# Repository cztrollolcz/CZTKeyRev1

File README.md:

# CZTKeyRev1
 
Acrylic cutting: https://www.sculpteo.com/en/shop/cart/

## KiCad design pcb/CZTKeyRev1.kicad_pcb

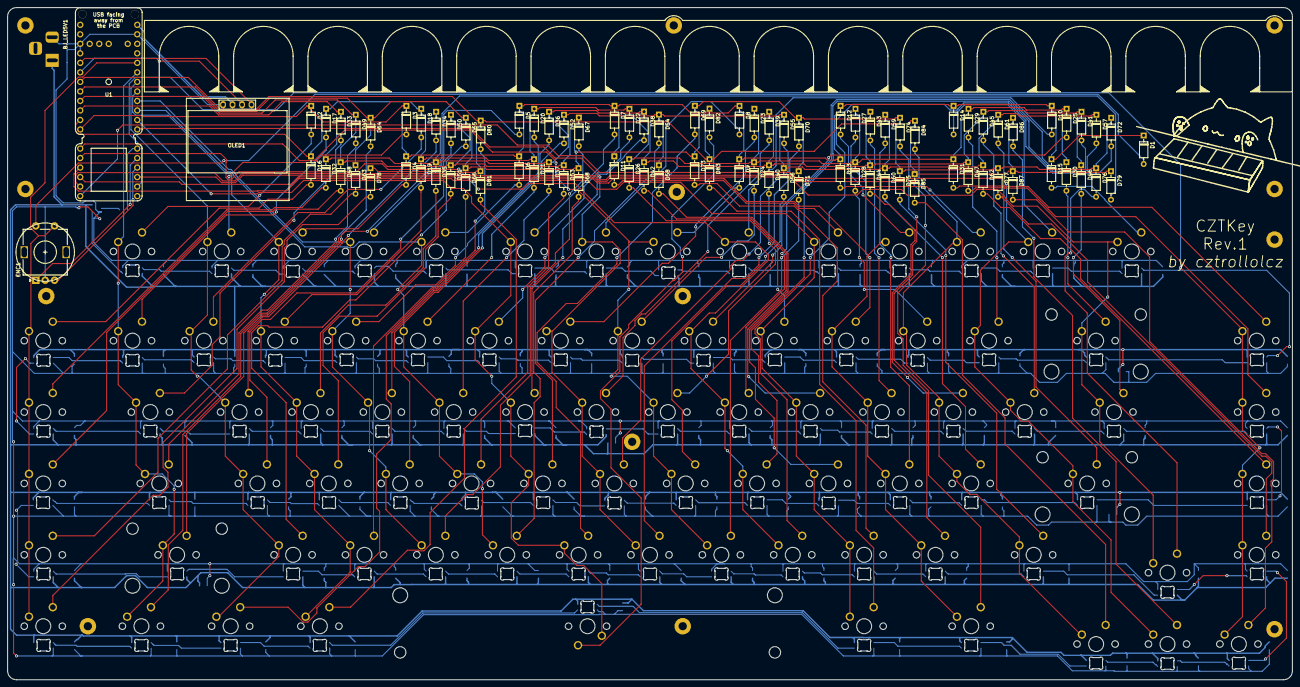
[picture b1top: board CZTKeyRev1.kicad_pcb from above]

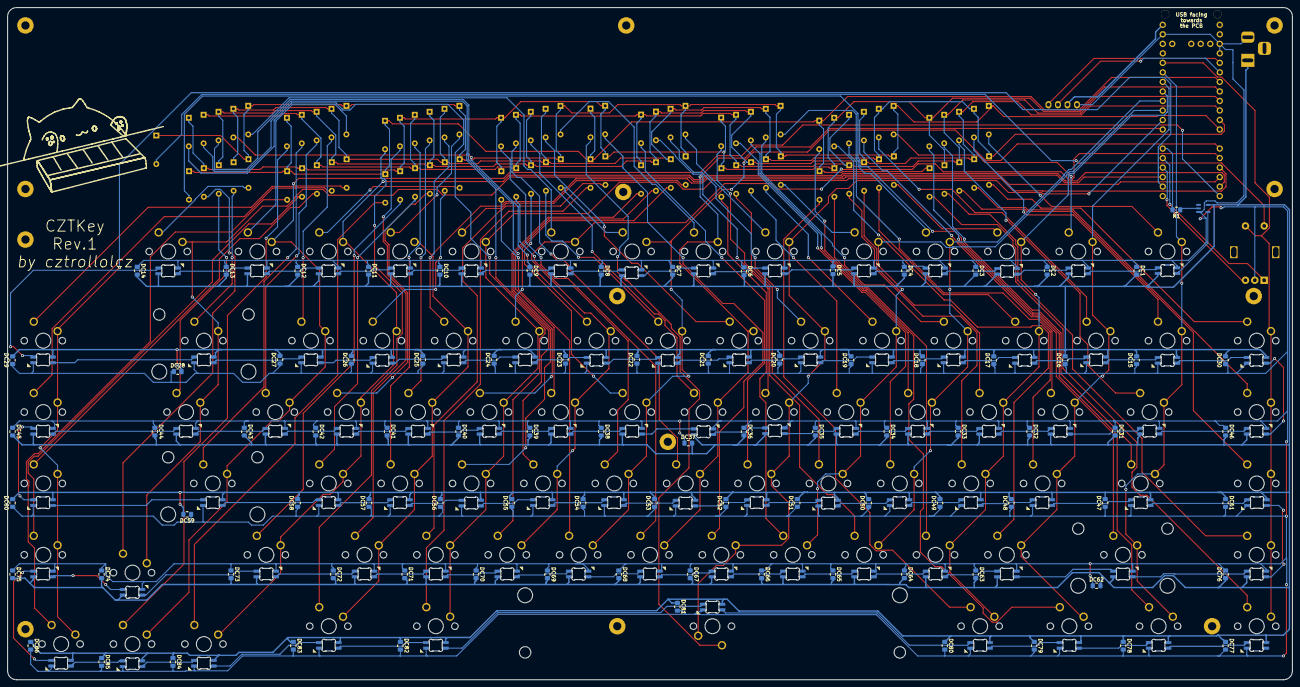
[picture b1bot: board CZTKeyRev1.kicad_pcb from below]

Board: 2 copper layers, 342.9 x 179.4 mm, 364 parts (88 on the bottom side), 204 nets.

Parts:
BJ_LED5V1: Barrel_Jack_Switch; BarrelJackP1
D1, D2, D3, D4, D5, D6, D7, D8, D9, D10, D11, D12, D13, D14, D15, D16, D17, D18, D19, D20, D21, D22, D23, D24, D25, D26, D27, D28, D29, D30, D31, D32, D33, D34, D35, D36, D37, D38, D39, D40, D41, D42, D43, D44, D45, D46, D47, D48, D49, D50, D51, D52, D53, D54, D55, D56, D57, D58, D59, D60, D61, D62, D63, D64, D65, D66, D67, D68, D69, D70, D71, D72, D73, D74, D75, D76, D77, D78, D79, D80, D81, D82, D83, D84, D85, D86, D87: D_Small; D_DO-35_SOD27_P7.62mm_Horizontal
DC1, DC2, DC3, DC4, DC5, DC6, DC7, DC8, DC9, DC10, DC11, DC12, DC13, DC14, DC15, DC16, DC17, DC18, DC19, DC20, DC21, DC22, DC23, DC24, DC25, DC26, DC27, DC28, DC29, DC30, DC31, DC32, DC33, DC34, DC35, DC36, DC37, DC38, DC39, DC40, DC41, DC42, DC43, DC44, DC45, DC46, DC47, DC48, DC49, DC50, DC51, DC52, DC53, DC54, DC55, DC56, DC57, DC58, DC59, DC60, DC61, DC62, DC63, DC64, DC65, DC66, DC67, DC68, DC69, DC70, DC71, DC72, DC73, DC74, DC75, DC76, DC77, DC78, DC79, DC80, DC81, DC82, DC83, DC84, DC85, DC86: 100n; C_0805_2012Metric_Pad1.15x1.40mm_HandSolder
ENC1: Rotary_Encoder_Switch; RotaryEncoder_Alps_EC11E-Switch_Vertical_H20mm
EXT_IC1: 74LVC1G17GV,125; SOT95P275X110-5N
LED1, LED2, LED3, LED4, LED5, LED6, LED7, LED8, LED9, LED10, LED11, LED12, LED13, LED14, LED15, LED16, LED17, LED18, LED19, LED20, LED21, LED22, LED23, LED24, LED25, LED26, LED27, LED28, LED29, LED30, LED31, LED32, LED33, LED34, LED35, LED36, LED37, LED38, LED39, LED40, LED41, LED42, LED43, LED44, LED45, LED46, LED47, LED48, LED49, LED50, LED51, LED52, LED53, LED54, LED55, LED56, LED57, LED58, LED59, LED60, LED61, LED62, LED63, LED64, LED65, LED66, LED67, LED68, LED69, LED70, LED71, LED72, LED73, LED74, LED75, LED76, LED77, LED78, LED79, LED80, LED81, LED82, LED83, LED84, LED85, LED86: YS-SK6812MINI-E; SK6812MINIE-simple
MX_1, MX_2, MX_3, MX_4, MX_5, MX_6, MX_7, MX_8, MX_9, MX_10: MX-NoLED; MXOnly-1U-NoLED
MX_A1: MX-NoLED; MXOnly-1U-NoLED
MX_ALT_L1: MX-NoLED; MXOnly-1.25U-NoLED
MX_ALT_R1: MX-NoLED; MXOnly-1.5U-NoLED
MX_B1: MX-NoLED; MXOnly-1U-NoLED
MX_BACKSPACE1: MX-NoLED; MXOnly-2U-NoLED
MX_BCKSLASH1: MX-NoLED; MXOnly-1.5U-NoLED
MX_BR_L1: MX-NoLED; MXOnly-1U-NoLED
MX_BR_R1: MX-NoLED; MXOnly-1U-NoLED
MX_C1: MX-NoLED; MXOnly-1U-NoLED
MX_CAPS1: MX-NoLED; MXOnly-1.75U-NoLED
MX_COMMA1: MX-NoLED; MXOnly-1U-NoLED
MX_CTRL_L1: MX-NoLED; MXOnly-1.25U-NoLED
MX_CTRL_R1: MX-NoLED; MXOnly-1.5U-NoLED
MX_D1: MX-NoLED; MXOnly-1U-NoLED
MX_DELETE1: MX-NoLED; MXOnly-1U-NoLED
MX_DOT1: MX-NoLED; MXOnly-1U-NoLED
MX_DOWN1: MX-NoLED; MXOnly-1U-NoLED
MX_E1: MX-NoLED; MXOnly-1U-NoLED
MX_ENTER1: MX-NoLED; MXOnly-2.25U-NoLED
MX_EQUAL1: MX-NoLED; MXOnly-1U-NoLED
MX_ESC1: MX-NoLED; MXOnly-1U-NoLED
MX_F1, MX_F2, MX_F3, MX_F4, MX_F5, MX_F6, MX_F7, MX_F8, MX_F9, MX_F10, MX_F11, MX_F12, MX_F13: MX-NoLED; MXOnly-1U-NoLED
MX_G1: MX-NoLED; MXOnly-1U-NoLED
MX_H1: MX-NoLED; MXOnly-1U-NoLED
MX_I1: MX-NoLED; MXOnly-1U-NoLED
MX_INSERT1: MX-NoLED; MXOnly-1U-NoLED
MX_J1: MX-NoLED; MXOnly-1U-NoLED
MX_K1: MX-NoLED; MXOnly-1U-NoLED
MX_L1: MX-NoLED; MXOnly-1U-NoLED
MX_LEFT1: MX-NoLED; MXOnly-1U-NoLED
MX_M1: MX-NoLED; MXOnly-1U-NoLED
MX_MAC1, MX_MAC2, MX_MAC3, MX_MAC4, MX_MAC5: MX-NoLED; MXOnly-1U-NoLED
MX_MINUS1: MX-NoLED; MXOnly-1U-NoLED
MX_N1: MX-NoLED; MXOnly-1U-NoLED
MX_O1: MX-NoLED; MXOnly-1U-NoLED
MX_P1: MX-NoLED; MXOnly-1U-NoLED
MX_PGDWN1: MX-NoLED; MXOnly-1U-NoLED
MX_PGUP1: MX-NoLED; MXOnly-1U-NoLED
MX_PRTSC1: MX-NoLED; MXOnly-1U-NoLED
MX_Q1: MX-NoLED; MXOnly-1U-NoLED
MX_QUOTE1: MX-NoLED; MXOnly-1U-NoLED
MX_R1: MX-NoLED; MXOnly-1U-NoLED
MX_RIGHT1: MX-NoLED; MXOnly-1U-NoLED
MX_S1: MX-NoLED; MXOnly-1U-NoLED
MX_SEMIC1: MX-NoLED; MXOnly-1U-NoLED
MX_SHIFT_L1: MX-NoLED; MXOnly-2.25U-NoLED
MX_SHIFT_R1: MX-NoLED; MXOnly-1.75U-NoLED
MX_SLASH1: MX-NoLED; MXOnly-1U-NoLED
MX_SPACE1: MX-NoLED; MXOnly-6.25U-NoLED
MX_T1: MX-NoLED; MXOnly-1U-NoLED
MX_TAB1: MX-NoLED; MXOnly-1.5U-NoLED
MX_TILDE1: MX-NoLED; MXOnly-1U-NoLED
MX_U1: MX-NoLED; MXOnly-1U-NoLED
MX_UP1: MX-NoLED; MXOnly-1U-NoLED
MX_V1: MX-NoLED; MXOnly-1U-NoLED
MX_W1: MX-NoLED; MXOnly-1U-NoLED
MX_WIN1: MX-NoLED; MXOnly-1.25U-NoLED
MX_X1: MX-NoLED; MXOnly-1U-NoLED
MX_Y1: MX-NoLED; MXOnly-1U-NoLED
MX_Z1: MX-NoLED; MXOnly-1U-NoLED
OLED1: SSD1306; 128x64OLED
PCB_BC1: MountingHole_Pad; MountingHole_2.2mm_M2_Pad
PCB_BL1: MountingHole_Pad; MountingHole_2.2mm_M2_Pad
PCB_BR1: MountingHole_Pad; MountingHole_2.2mm_M2_Pad
PCB_MC1: MountingHole_Pad; MountingHole_2.2mm_M2_Pad
PCB_TC1: MountingHole_Pad; MountingHole_2.2mm_M2_Pad
PCB_TL1: MountingHole_Pad; MountingHole_2.2mm_M2_Pad
PCB_TR1: MountingHole_Pad; MountingHole_2.2mm_M2_Pad
PLATE_BC1: MountingHole_Pad; MountingHole_2.2mm_M2_Pad
PLATE_BL1: MountingHole_Pad; MountingHole_2.2mm_M2_Pad
PLATE_BR1: MountingHole_Pad; MountingHole_2.2mm_M2_Pad
PLATE_TC1: MountingHole_Pad; MountingHole_2.2mm_M2_Pad
PLATE_TL1: MountingHole_Pad; MountingHole_2.2mm_M2_Pad
PLATE_TR1: MountingHole_Pad; MountingHole_2.2mm_M2_Pad
R1: 300-500 - C422828; R_0805_2012Metric_Pad1.15x1.40mm_HandSolder
U1: proton_c

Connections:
+5V: OLED1.2, U1.5V
COL0: ENC1.S1, MX_MAC1.1, MX_MAC2.1, MX_MAC3.1, MX_MAC4.1, MX_MAC5.1, U1.A2
COL1: MX_CAPS1.1, MX_CTRL_L1.1, MX_ESC1.1, MX_SHIFT_L1.1, MX_TAB1.1, MX_TILDE1.1, U1.A1
COL2: MX_1.1, MX_A1.1, MX_F1.1, MX_Q1.1, MX_WIN1.1, MX_Z1.1, U1.A0
COL3: MX_2.1, MX_ALT_L1.1, MX_F2.1, MX_S1.1, MX_W1.1, MX_X1.1, U1.B8
COL4: MX_3.1, MX_C1.1, MX_D1.1, MX_E1.1, MX_F3.1, U1.B13
COL5: MX_4.1, MX_F4.1, MX_F13.1, MX_R1.1, MX_V1.1, U1.B14
COL6: MX_5.1, MX_B1.1, MX_F5.1, MX_G1.1, MX_SPACE1.1, MX_T1.1, U1.B15
COL7: MX_6.1, MX_F6.1, MX_H1.1, MX_N1.1, MX_Y1.1, U1.B9
COL8: MX_7.1, MX_F7.1, MX_J1.1, MX_M1.1, MX_U1.1, U1.A4
COL9: MX_8.1, MX_COMMA1.1, MX_F8.1, MX_I1.1, MX_K1.1, U1.A5
COL10: MX_9.1, MX_ALT_R1.1, MX_DOT1.1, MX_F9.1, MX_L1.1, MX_O1.1, U1.A6
COL11: MX_10.1, MX_CTRL_R1.1, MX_F10.1, MX_P1.1, MX_SEMIC1.1, MX_SLASH1.1, U1.A7
COL12: MX_BR_R1.1, MX_F11.1, MX_LEFT1.1, MX_MINUS1.1, MX_QUOTE1.1, MX_SHIFT_R1.1, U1.A8
COL13: MX_BR_L1.1, MX_DOWN1.1, MX_ENTER1.1, MX_EQUAL1.1, MX_F12.1, U1.A15
COL14: MX_BACKSPACE1.1, MX_BCKSLASH1.1, MX_PRTSC1.1, MX_UP1.1, U1.A14
COL15: MX_DELETE1.1, MX_INSERT1.1, MX_PGDWN1.1, MX_PGUP1.1, MX_RIGHT1.1, U1.A13
ENC_A: ENC1.A, U1.B11
ENC_B: ENC1.B, U1.B12
ENC_S2: D1.2, ENC1.S2
EXT_5V: BJ_LED5V1.1, DC1.2, DC2.2, DC3.2, DC4.2, DC5.2, DC6.2, DC7.2, DC8.2, DC9.2, DC10.2, DC11.2, DC12.2, DC13.2, DC14.2, DC15.2, DC16.2, DC17.2, DC18.2, DC19.2, DC20.2, DC21.2, DC22.2, DC23.2, DC24.2, DC25.2, DC26.2, DC27.2, DC28.2, DC29.2, DC30.2, DC31.2, DC32.2, DC33.2, DC34.2, DC35.2, DC36.2, DC37.2, DC38.2, DC39.2, DC40.2, DC41.2, DC42.2, DC43.2, DC44.2, DC45.2, DC46.2, DC47.2, DC48.2, DC49.2, DC50.2, DC51.2, DC52.2, DC53.2, DC54.2, DC55.2, DC56.2, DC57.2, DC58.2, DC59.2, DC60.2, DC61.1, DC62.2, DC63.2, DC64.2, DC65.2, DC66.2, DC67.2, DC68.2, DC69.2, DC70.2, DC71.2, DC72.2, DC73.2, DC74.2, DC75.2, DC76.1, DC77.1, DC78.1, DC79.1, DC80.1, DC81.1, DC82.1, DC83.1, DC84.1, DC85.1, DC86.1, EXT_IC1.5, LED1.1, LED2.1, LED3.1, LED4.1, LED5.1, LED6.1, LED7.1, LED8.1, LED9.1, LED10.1, LED11.1, LED12.1, LED13.1, LED14.1, LED15.1, LED16.1, LED17.1, LED18.1, LED19.1, LED20.1, LED21.1, LED22.1, LED23.1, LED24.1, LED25.1, LED26.1, LED27.1, LED28.1, LED29.1, LED30.1, LED31.1, LED32.1, LED33.1, LED34.1, LED35.1, LED36.1, LED37.1, LED38.1, LED39.1, LED40.1, LED41.1, LED42.1, LED43.1, LED44.1, LED45.1, LED46.1, LED47.1, LED48.1, LED49.1, LED50.1, LED51.1, LED52.1, LED53.1, LED54.1, LED55.1, LED56.1, LED57.1, LED58.1, LED59.1, LED60.1, LED61.1, LED62.1, LED63.1, LED64.1, LED65.1, LED66.1, LED67.1, LED68.1, LED69.1, LED70.1, LED71.1, LED72.1, LED73.1, LED74.1, LED75.1, LED76.1, LED77.1, LED78.1, LED79.1, LED80.1, LED81.1, LED82.1, LED83.1, LED84.1, LED85.1, LED86.1
GND: BJ_LED5V1.2, DC1.1, DC2.1, DC3.1, DC4.1, DC5.1, DC6.1, DC7.1, DC8.1, DC9.1, DC10.1, DC11.1, DC12.1, DC13.1, DC14.1, DC15.1, DC16.1, DC17.1, DC18.1, DC19.1, DC20.1, DC21.1, DC22.1, DC23.1, DC24.1, DC25.1, DC26.1, DC27.1, DC28.1, DC29.1, DC30.1, DC31.1, DC32.1, DC33.1, DC34.1, DC35.1, DC36.1, DC37.1, DC38.1, DC39.1, DC40.1, DC41.1, DC42.1, DC43.1, DC44.1, DC45.1, DC46.1, DC47.1, DC48.1, DC49.1, DC50.1, DC51.1, DC52.1, DC53.1, DC54.1, DC55.1, DC56.1, DC57.1, DC58.1, DC59.1, DC60.1, DC61.2, DC62.1, DC63.1, DC64.1, DC65.1, DC66.1, DC67.1, DC68.1, DC69.1, DC70.1, DC71.1, DC72.1, DC73.1, DC74.1, DC75.1, DC76.2, DC77.2, DC78.2, DC79.2, DC80.2, DC81.2, DC82.2, DC83.2, DC84.2, DC85.2, DC86.2, ENC1.C, EXT_IC1.3, LED1.3, LED2.3, LED3.3, LED4.3, LED5.3, LED6.3, LED7.3, LED8.3, LED9.3, LED10.3, LED11.3, LED12.3, LED13.3, LED14.3, LED15.3, LED16.3, LED17.3, LED18.3, LED19.3, LED20.3, LED21.3, LED22.3, LED23.3, LED24.3, LED25.3, LED26.3, LED27.3, LED28.3, LED29.3, LED30.3, LED31.3, LED32.3, LED33.3, LED34.3, LED35.3, LED36.3, LED37.3, LED38.3, LED39.3, LED40.3, LED41.3, LED42.3, LED43.3, LED44.3, LED45.3, LED46.3, LED47.3, LED48.3, LED49.3, LED50.3, LED51.3, LED52.3, LED53.3, LED54.3, LED55.3, LED56.3, LED57.3, LED58.3, LED59.3, LED60.3, LED61.3, LED62.3, LED63.3, LED64.3, LED65.3, LED66.3, LED67.3, LED68.3, LED69.3, LED70.3, LED71.3, LED72.3, LED73.3, LED74.3, LED75.3, LED76.3, LED77.3, LED78.3, LED79.3, LED80.3, LED81.3, LED82.3, LED83.3, LED84.3, LED85.3, LED86.3, OLED1.1, U1.GND
unnamed: D2.2, MX_ESC1.2
unnamed: D3.2, MX_F1.2
unnamed: D4.2, MX_F2.2
unnamed: D5.2, MX_F3.2
unnamed: D6.2, MX_F4.2
unnamed: D7.2, MX_F5.2
unnamed: D8.2, MX_F6.2
unnamed: D9.2, MX_F7.2
unnamed: D10.2, MX_F8.2
unnamed: D11.2, MX_F9.2
unnamed: D12.2, MX_F10.2
unnamed: D13.2, MX_F11.2
unnamed: D14.2, MX_F12.2
unnamed: D15.2, MX_PRTSC1.2
unnamed: D16.2, MX_MAC1.2
unnamed: D17.2, MX_TILDE1.2
unnamed: D18.2, MX_1.2
unnamed: D19.2, MX_2.2
unnamed: D20.2, MX_3.2
unnamed: D21.2, MX_4.2
unnamed: D22.2, MX_5.2
unnamed: D23.2, MX_6.2
unnamed: D24.2, MX_7.2
unnamed: D25.2, MX_8.2
unnamed: D26.2, MX_9.2
unnamed: D27.2, MX_10.2
unnamed: D28.2, MX_MINUS1.2
unnamed: D29.2, MX_EQUAL1.2
unnamed: D30.2, MX_BACKSPACE1.2
unnamed: D31.2, MX_INSERT1.2
unnamed: D32.2, MX_MAC2.2
unnamed: D33.2, MX_TAB1.2
unnamed: D34.2, MX_Q1.2
unnamed: D35.2, MX_W1.2
unnamed: D36.2, MX_E1.2
unnamed: D37.2, MX_R1.2
unnamed: D38.2, MX_T1.2
unnamed: D39.2, MX_Y1.2
unnamed: D40.2, MX_U1.2
unnamed: D41.2, MX_I1.2
unnamed: D42.2, MX_O1.2
unnamed: D43.2, MX_P1.2
unnamed: D44.2, MX_BR_R1.2
unnamed: D45.2, MX_BR_L1.2
unnamed: D46.2, MX_BCKSLASH1.2
unnamed: D47.2, MX_DELETE1.2
unnamed: D48.2, MX_MAC3.2
unnamed: D49.2, MX_CAPS1.2
unnamed: D50.2, MX_A1.2
unnamed: D51.2, MX_S1.2
unnamed: D52.2, MX_D1.2
unnamed: D53.2, MX_F13.2
unnamed: D54.2, MX_G1.2
unnamed: D55.2, MX_H1.2
unnamed: D56.2, MX_J1.2
unnamed: D57.2, MX_K1.2
unnamed: D58.2, MX_L1.2
unnamed: D59.2, MX_SEMIC1.2
unnamed: D60.2, MX_QUOTE1.2
unnamed: D61.2, MX_ENTER1.2
unnamed: D62.2, MX_PGUP1.2
unnamed: D63.2, MX_MAC4.2
unnamed: D64.2, MX_SHIFT_L1.2
unnamed: D65.2, MX_Z1.2
unnamed: D66.2, MX_X1.2
unnamed: D67.2, MX_C1.2
unnamed: D68.2, MX_V1.2
unnamed: D69.2, MX_B1.2
unnamed: D70.2, MX_N1.2
unnamed: D71.2, MX_M1.2
unnamed: D72.2, MX_COMMA1.2
unnamed: D73.2, MX_DOT1.2
unnamed: D74.2, MX_SLASH1.2
unnamed: D75.2, MX_SHIFT_R1.2
unnamed: D76.2, MX_UP1.2
unnamed: D77.2, MX_PGDWN1.2
unnamed: D78.2, MX_MAC5.2
unnamed: D79.2, MX_CTRL_L1.2
unnamed: D80.2, MX_WIN1.2
unnamed: D81.2, MX_ALT_L1.2
unnamed: D82.2, MX_SPACE1.2
unnamed: D83.2, MX_ALT_R1.2
unnamed: D84.2, MX_CTRL_R1.2
unnamed: D85.2, MX_LEFT1.2
unnamed: D86.2, MX_DOWN1.2
unnamed: D87.2, MX_RIGHT1.2
unnamed: EXT_IC1.4, LED1.4
unnamed: LED1.2, LED2.4
unnamed: LED2.2, LED3.4
unnamed: LED3.2, LED4.4
unnamed: LED4.2, LED5.4
unnamed: LED5.2, LED6.4
unnamed: LED6.2, LED7.4
unnamed: LED7.2, LED8.4
unnamed: LED8.2, LED9.4
unnamed: LED10.2, LED11.4
unnamed: LED9.2, LED10.4
unnamed: LED11.2, LED12.4
unnamed: LED12.2, LED13.4
unnamed: LED13.2, LED14.4
unnamed: LED14.2, LED30.4
unnamed: LED15.2, LED31.4
unnamed: LED15.4, LED16.2
unnamed: LED16.4, LED17.2
unnamed: LED17.4, LED18.2
unnamed: LED18.4, LED19.2
unnamed: LED19.4, LED20.2
unnamed: LED20.4, LED21.2
unnamed: LED21.4, LED22.2
unnamed: LED22.4, LED23.2
unnamed: LED23.4, LED24.2
unnamed: LED24.4, LED25.2
unnamed: LED25.4, LED26.2
unnamed: LED26.4, LED27.2
unnamed: LED27.4, LED28.2
unnamed: LED28.4, LED29.2
unnamed: LED29.4, LED30.2
unnamed: LED31.2, LED32.4
unnamed: LED32.2, LED33.4
unnamed: LED33.2, LED34.4
unnamed: LED34.2, LED35.4
unnamed: LED35.2, LED36.4
unnamed: LED36.2, LED37.4
unnamed: LED37.2, LED38.4
unnamed: LED38.2, LED39.4
unnamed: LED39.2, LED40.4
unnamed: LED40.2, LED41.4
unnamed: LED41.2, LED42.4
unnamed: LED42.2, LED43.4
unnamed: LED43.2, LED44.4
unnamed: LED44.2, LED45.4
unnamed: LED45.2, LED46.4
unnamed: LED46.2, LED61.4
unnamed: LED47.2, LED62.4
unnamed: LED47.4, LED48.2
unnamed: LED48.4, LED49.2
unnamed: LED49.4, LED50.2
unnamed: LED50.4, LED51.2
unnamed: LED51.4, LED52.2
unnamed: LED52.4, LED53.2
unnamed: LED53.4, LED54.2
unnamed: LED54.4, LED55.2
unnamed: LED55.4, LED56.2
unnamed: LED56.4, LED57.2
unnamed: LED57.4, LED58.2
unnamed: LED58.4, LED59.2
unnamed: LED59.4, LED60.2
unnamed: LED60.4, LED61.2
unnamed: LED62.2, LED63.4
unnamed: LED63.2, LED64.4
unnamed: LED64.2, LED65.4
unnamed: LED65.2, LED66.4
unnamed: LED66.2, LED67.4
unnamed: LED67.2, LED68.4
unnamed: LED68.2, LED69.4
unnamed: LED69.2, LED70.4
unnamed: LED70.2, LED71.4
unnamed: LED71.2, LED72.4
unnamed: LED72.2, LED73.4
unnamed: LED73.2, LED74.4
unnamed: LED74.2, LED75.4
unnamed: LED75.2, LED76.4
unnamed: LED76.2, LED86.4
unnamed: LED77.4, LED78.2
unnamed: LED78.4, LED79.2
unnamed: LED79.4, LED80.2
unnamed: LED80.4, LED81.2
unnamed: LED81.4, LED82.2
unnamed: LED82.4, LED83.2
unnamed: LED83.4, LED84.2
unnamed: LED84.4, LED85.2
unnamed: LED85.4, LED86.2
unnamed: R1.2, U1.B10
OLEDSCL: OLED1.3, U1.B6
OLEDSDA: OLED1.4, U1.B7
RGB_MATRIX: EXT_IC1.2, R1.1
ROW0: D1.1, D2.1, D3.1, D4.1, D5.1, D6.1, D7.1, D8.1, D9.1, D10.1, D11.1, D12.1, D13.1, D14.1, D15.1, U1.B0
ROW1: D16.1, D17.1, D18.1, D19.1, D20.1, D21.1, D22.1, D23.1, D24.1, D25.1, D26.1, D27.1, D28.1, D29.1, D30.1, D31.1, U1.B1
ROW2: D32.1, D33.1, D34.1, D35.1, D36.1, D37.1, D38.1, D39.1, D40.1, D41.1, D42.1, D43.1, D44.1, D45.1, D46.1, D47.1, U1.B2
ROW3: D48.1, D49.1, D50.1, D51.1, D52.1, D53.1, D54.1, D55.1, D56.1, D57.1, D58.1, D59.1, D60.1, D61.1, D62.1, U1.B3
ROW4: D63.1, D64.1, D65.1, D66.1, D67.1, D68.1, D69.1, D70.1, D71.1, D72.1, D73.1, D74.1, D75.1, D76.1, D77.1, U1.B4
ROW5: D78.1, D79.1, D80.1, D81.1, D82.1, D83.1, D84.1, D85.1, D86.1, D87.1, U1.B5

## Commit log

2020-12-14 PCB Mostly done
2020-12-14 Changed footprints
2020-12-20 Acrylic cutting service
